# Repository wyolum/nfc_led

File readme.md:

# NFC_LED
An LED that lights up in the presence of a NFC or similar radio signal (approx 13MHz).
To be made using flex-pcb material.

License
-------
[CERN Open Hardware Licence v1.2 ]

[CERN Open Hardware Licence v1.2 ]:http://www.ohwr.org/attachments/2388/cern_ohl_v_1_2.txt

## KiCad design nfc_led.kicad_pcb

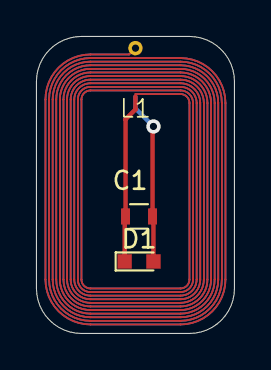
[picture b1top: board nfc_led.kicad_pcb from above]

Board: 2 copper layers, 11.0 x 16.5 mm, 3 parts (0 on the bottom side), 2 nets.

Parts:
C1: C; L_0603
D1: LED_ALT; LED_0603
L1: INDUCTOR; ant_nfc

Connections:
/HI: C1.1, D1.2, L1.2
/LO: C1.2, D1.1, L1.1

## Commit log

2018-05-09 initial push
2018-05-09 added readme
